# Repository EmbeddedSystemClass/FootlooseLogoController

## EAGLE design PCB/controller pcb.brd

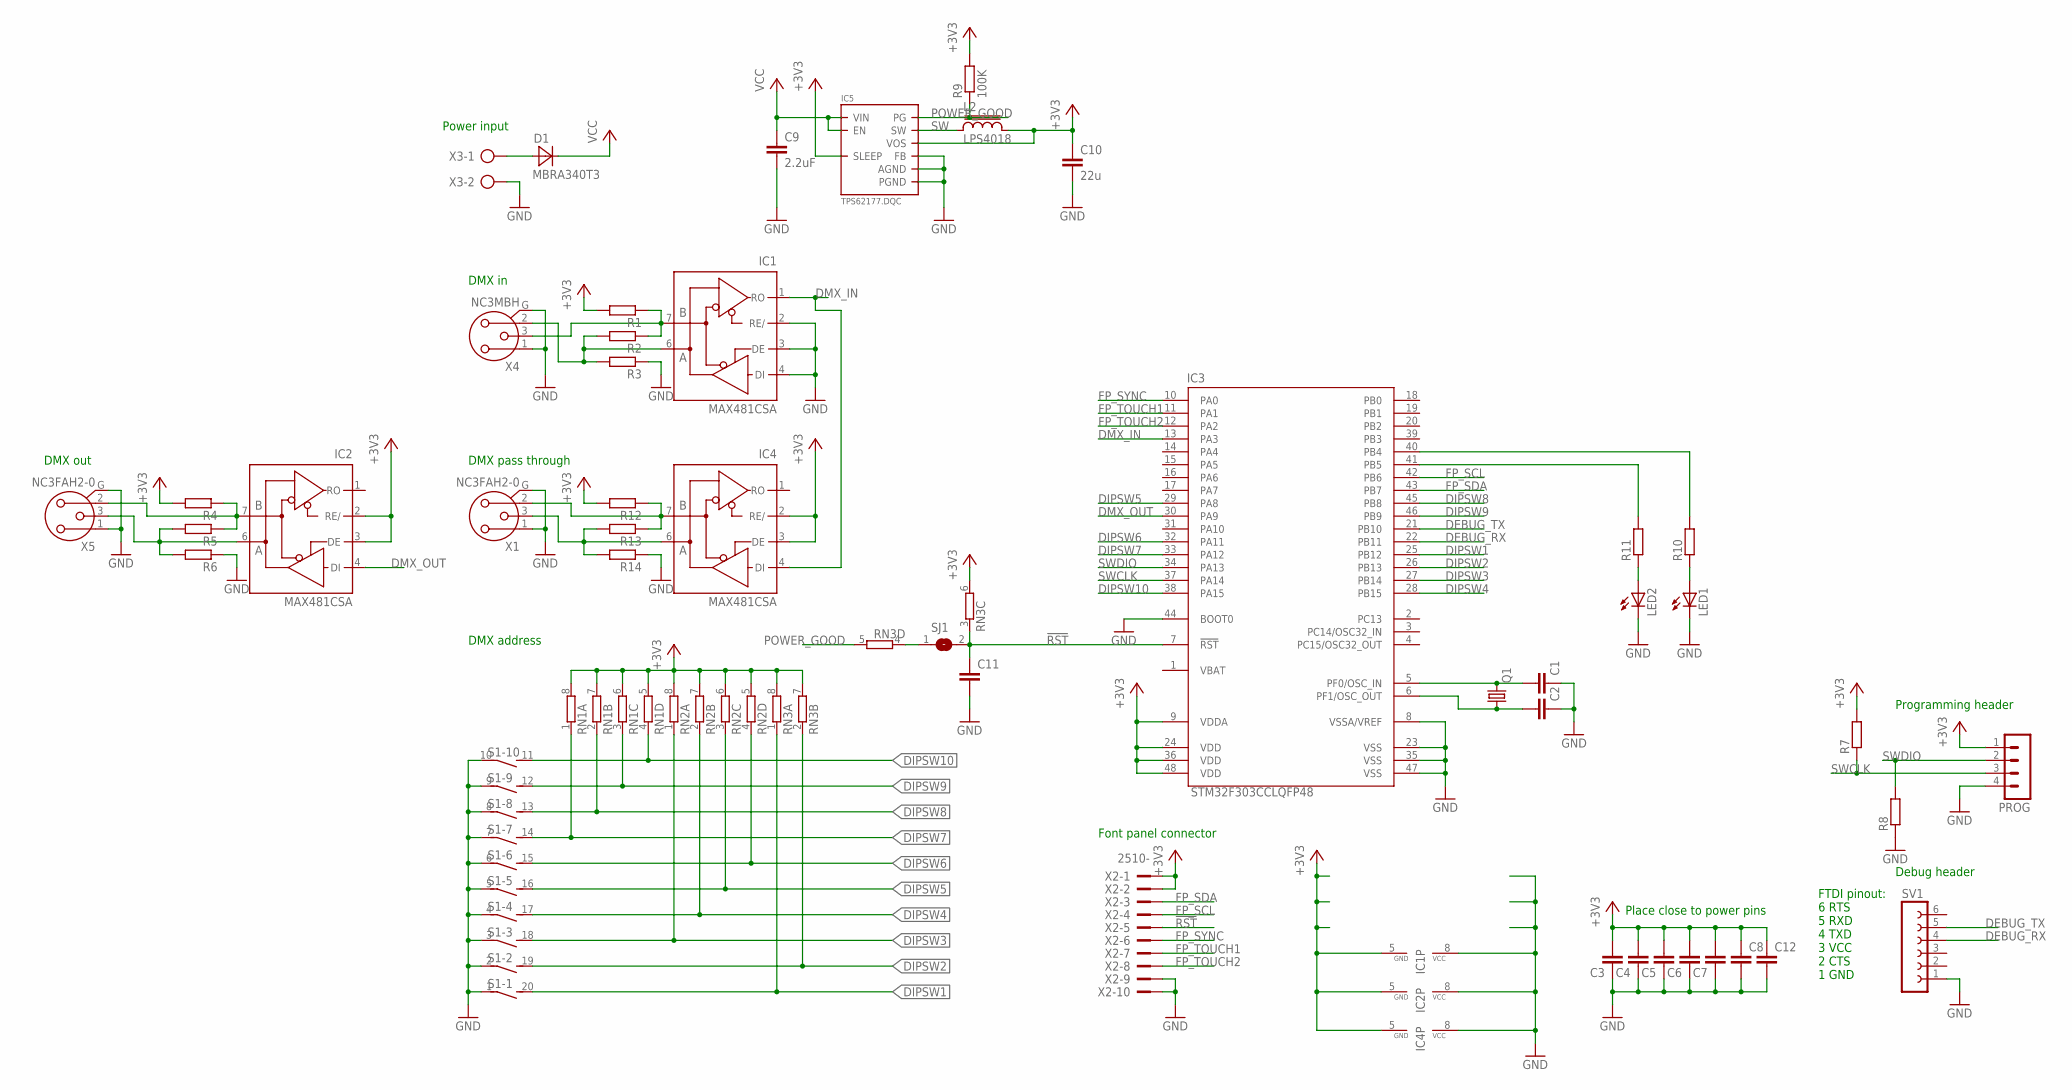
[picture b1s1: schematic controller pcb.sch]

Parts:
C1, C2, C3, C4, C5, C6, C7, C8, C11, C12: C-EUC0603K; C0603K
C9: 2.2uF; C1206
C10: 22u; C1206
D1: MBRA340T3; SMA
IC1, IC2, IC4: MAX481CSA; SO08
IC3: STM32F303CCLQFP48; LQFP48
IC5: TPS62177.DQC; DQC
L2: LPS4018
LED1, LED2: LEDCHIPLED_1206; CHIPLED_1206
PROG: MA04-1
Q1: CRYSTALCTS406; CTS406
R1, R2, R3, R4, R5, R6, R7, R8, R10, R11, R12, R13, R14: R-EU_R0603; R0603
R9: 100K; R0603
RN1, RN2, RN3: 4R-NCAY16; CAY16
S1: DIP10SB
SJ1: SJ
SV1: FE06-1; FE06
X1, X5: NC3FAH2-0
X2: 2510-; PAK100/2500-10
X3: AK500/2
X4: NC3MBH

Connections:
!RST: C11.1, IC3.7 (!RST), RN3.3 (1), SJ1.2, X2.5
+3V3: C3.2, C4.2, C5.2, C6.2, C7.2, C8.1, C10.1, C12.1, IC1.5 (GND), IC2.2 (RE/), IC2.3 (DE), IC2.5 (GND), IC3.9 (VDDA), IC3.24 (VDD), IC3.36 (VDD), IC3.48 (VDD), IC4.2 (RE/), IC4.3 (DE), IC4.5 (GND), IC5.8 (SLEEP), IC5.10 (VOS), L2.2, PROG.1, R1.2, R4.2, R7.2, R9.2, R12.2, RN1.5 (2), RN1.6 (2), RN1.7 (2), RN1.8 (2), RN2.5 (2), RN2.6 (2), RN2.7 (2), RN2.8 (2), RN3.6 (2), RN3.7 (2), RN3.8 (2), X2.1, X2.2
DEBUG_RX: IC3.22 (PB11), SV1.4
DEBUG_TX: IC3.21 (PB10), SV1.5
DIPSW1: IC3.25 (PB12), RN3.1, S1.20 (2)
DIPSW2: IC3.26 (PB13), RN3.2 (1), S1.19 (2)
DIPSW3: IC3.27 (PB14), RN2.1, S1.18 (2)
DIPSW4: IC3.28 (PB15), RN2.2 (1), S1.17 (2)
DIPSW5: IC3.29 (PA8), RN2.3 (1), S1.16 (2)
DIPSW6: IC3.32 (PA11), RN2.4 (1), S1.15 (2)
DIPSW7: IC3.33 (PA12), RN1.1, S1.14 (2)
DIPSW8: IC3.45 (PB8), RN1.2 (1), S1.13 (2)
DIPSW9: IC3.46 (PB9), RN1.3 (1), S1.12 (2)
DIPSW10: IC3.38 (PA15), RN1.4 (1), S1.11 (2)
DMX_IN: IC1.1 (RO), IC3.13 (PA3), IC4.4 (DI)
DMX_OUT: IC2.4 (DI), IC3.30 (PA9)
FP_SCL: IC3.42 (PB6), X2.4
FP_SDA: IC3.43 (PB7), X2.3
FP_SYNC: IC3.10 (PA0), X2.6
FP_TOUCH1: IC3.11 (PA1), X2.7
FP_TOUCH2: IC3.12 (PA2), X2.8
GND: C1.1, C2.1, C3.1, C4.1, C5.1, C6.1, C7.1, C8.2, C9.2, C10.2, C11.2, C12.2, IC1.2 (RE/), IC1.3 (DE), IC1.4 (DI), IC1.8 (VCC), IC2.8 (VCC), IC3.8 (VSSA/VREF), IC3.23 (VSS), IC3.35 (VSS), IC3.44 (BOOT0), IC3.47 (VSS), IC4.8 (VCC), IC5.1 (PGND), IC5.5 (FB), IC5.6 (AGND), IC5.PAD (PGND), LED1.C, LED2.C, PROG.4, R3.1, R6.1, R8.1, R14.1, S1.1, S1.2 (1), S1.3 (1), S1.4 (1), S1.5 (1), S1.6 (1), S1.7 (1), S1.8 (1), S1.9 (1), S1.10 (1), SV1.1, X1.1, X1.G, X2.9, X2.10, X3.2, X4.1, X4.G, X5.1, X5.G
unnamed: D1.A, X3.1
unnamed: IC4.6 (A), R13.2, R14.2, X1.3
unnamed: IC1.7 (B), R1.1, R2.1, X4.3
unnamed: C2.2, IC3.6 (PF1/OSC_OUT), Q1.1
unnamed: C1.2, IC3.5 (PF0/OSC_IN), Q1.3 (2)
unnamed: IC2.6 (A), R5.2, R6.2, X5.3
unnamed: IC2.7 (B), R4.1, R5.1, X5.2
unnamed: LED1.A, R10.1
unnamed: LED2.A, R11.1
unnamed: IC3.41 (PB5), R11.2
unnamed: IC3.40 (PB4), R10.2
unnamed: RN3.4 (1), SJ1.1
unnamed: IC4.7 (B), R12.1, R13.1, X1.2
unnamed: IC1.6 (A), R2.2, R3.2, X4.2
POWER_GOOD: IC5.7 (PG), R9.1, RN3.5 (2)
SW: IC5.9 (SW), L2.1
SWCLK: IC3.37 (PA14), PROG.3, R7.1
SWDIO: IC3.34 (PA13), PROG.2, R8.2
VCC: C9.1, D1.C, IC5.2 (VIN), IC5.3 (EN)

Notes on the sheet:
Power input
DMX in
DMX out
DMX address
Font panel connector
Place close to power pins
Debug header
FTDI pinout: 6 RTS 5 RXD 4 TXD 3 VCC 2 CTS 1 GND
Programming header
DMX pass through

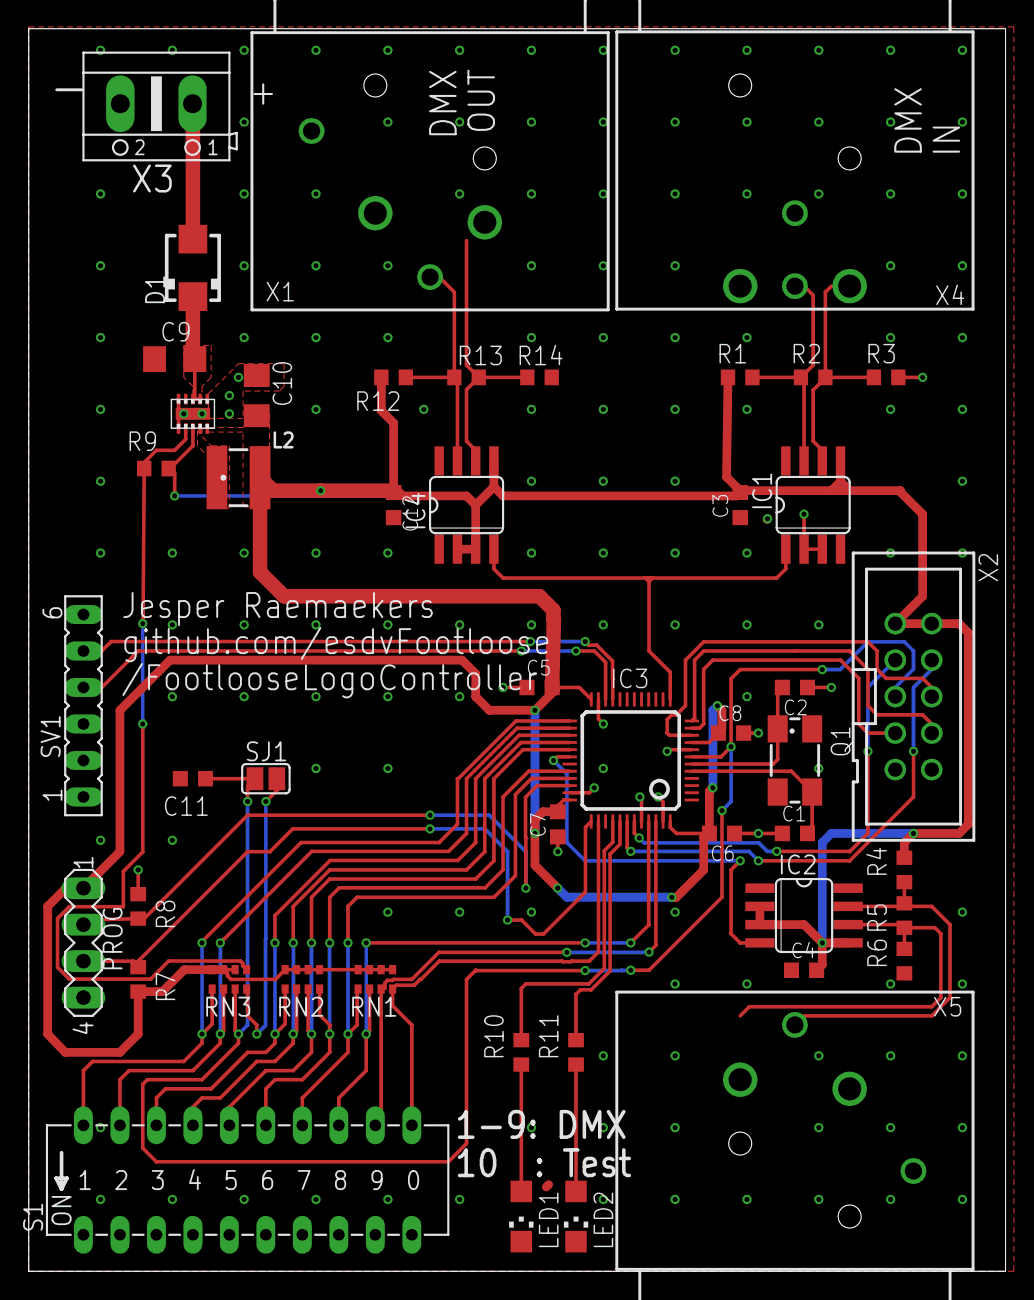
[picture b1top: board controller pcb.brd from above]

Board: 2 copper layers, 68.0 x 86.5 mm, 48 parts (0 on the bottom side), 41 nets.

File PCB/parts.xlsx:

Partlist
Exported from controller pcb.sch at 25/02/2019 09:50
EAGLE Version 9.3.0 Copyright (c) 1988-2019 Autodesk, Inc.
Assembly variant:
Part | Value | Device | Package | Library | Sheet | farnell code | amount
C1, C2 | 22pF | C-EUC0603K | C0603K | rcl | 1 | 2533830
C3, C4, C5, C6, C7, C8, C12 | 100nF | C-EUC0603K | C0603K | rcl | 1 | 2522395
C9 | 2.2uF | C-EUC1206 | C1206 | rcl | 1 | 1458911
C10 | 22u | C-EUC1206 | C1206 | rcl | 1
C11 | No | C-EUC0603K | C0603K | rcl | 1
D1 | MBRA340T3 | MBRA340T3 | SMA | diode | 1
IC1, IC2, IC4 | MAX481CSA | MAX481CSA | SO08 | maxim | 1 | 2519249
IC3 | STM32F303CCLQFP48 | STM32F303CCLQFP48 | LQFP48 | comp | 1 | 2215113
IC5 | TPS62177.DQC | TPS62177.DQC | DQC | packages(ti) | 1
L2 | LPS4018 | LPS4018 | LPS4018 | inductor-coilcraft | 1 | 2408076
LED1 |  | LEDCHIPLED_1206 | CHIPLED_1206 | led | 1 | 2099247
LED2 |  | LEDCHIPLED_1206 | CHIPLED_1206 | led | 1 | 2290336
PROG | Header 4P | MA04-1 | MA04-1 | con-lstb | 1
Q1 | 8MHz | CRYSTALCTS406 | CTS406 | crystal | 1
R1, R2, R3, R4, R5, R6, R12, R13, R14 |  | R-EU_R0603 | R0603 | rcl | 1
R7 |  | R-EU_R0603 | R0603 | rcl | 1
R8 |  | R-EU_R0603 | R0603 | rcl | 1
R9 | 100K | R-EU_R0603 | R0603 | rcl | 1
R10, R11 | 100 | R-EU_R0603 | R0603 | rcl | 1
RN1, RN2, RN3 | 4K7 | 4R-NCAY16 | CAY16 | resistor-dil | 1 | 2321746
S1 |  | DIP10SB | DIP10SB | switch-dil | 1 | 2468732
SV1 | Header 6P | FE06-1 | FE06 | con-lsta | 1
X1, X5 | NC3FAH2-0 | NC3FAH2-0 | NC3FAH2-0 | con-neutrik_ag | 1
X2 | Boxed header 10p | -2510 | PAK100/2500-10 | con-3m | 1
X3 | Power 2P | AK500/2 | AK500/2 | con-ptr500 | 1
X4 | NC3MBH | NC3MBH | NC3MBH | con-neutrik_ag | 1

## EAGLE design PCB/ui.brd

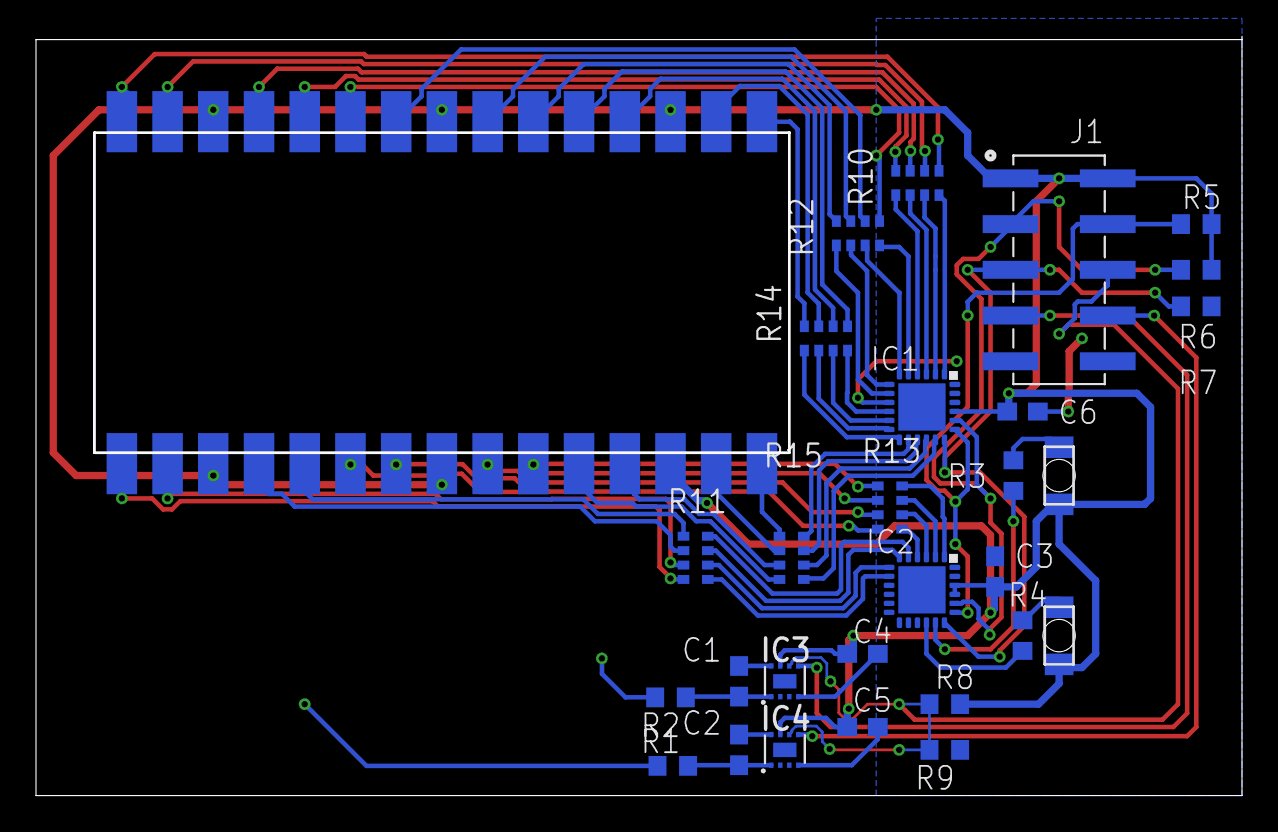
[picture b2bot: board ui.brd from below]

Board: 2 copper layers, 66.8 x 42.0 mm, 31 parts (26 on the bottom side), 64 nets.

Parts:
C1, C2, C3, C4, C5, C6: C0603
D1, D2: KPTL-3216; LED-REV
IC1, IC2: CAT9532; TQFN24-EP
IC3, IC4: AT42QT1011; UDFN/USON_8_PAD
J1: 610X1021121
R1, R2, R3, R4, R5, R6, R7, R8, R9: R0603
R10, R11, R12, R13, R14, R15: CAT16
SEG1, SEG2, SEG3: KCSA56-105; KCSA56-REV

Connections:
!RESET: IC1.18, IC2.18, J1.5, R7.2
+3V3: C3.1, C4.1, C5.1, C6.1, D1.P$1, D2.P$1, IC1.21, IC2.21, IC2.22, IC3.7, IC4.7, J1.1, J1.2, R5.2, R6.2, R8.2, SEG1.P3, SEG1.P8, SEG2.P3, SEG2.P8, SEG3.P3, SEG3.P8
GND: C3.2, C4.2, C5.2, C6.2, IC1.9, IC1.22, IC1.23, IC1.24, IC2.9, IC2.23, IC2.24, IC3.4, IC4.4, J1.9, J1.10, R7.1, R9.1
LED_PWR: IC2.17, R3.2
LED_STATUS: IC2.16, R4.2
unnamed: R10.8, SEG1.P10
unnamed: R10.7, SEG1.P9
unnamed: R10.6, SEG1.P7
unnamed: R10.5, SEG1.P6
unnamed: R12.8, SEG2.P10
unnamed: R12.7, SEG2.P9
unnamed: R12.6, SEG2.P7
unnamed: R12.5, SEG2.P6
unnamed: R14.8, SEG3.P10
unnamed: R14.7, SEG3.P9
unnamed: R14.6, SEG3.P7
unnamed: R14.5, SEG3.P6
unnamed: R11.8, SEG1.P5
unnamed: R11.7, SEG1.P4
unnamed: R11.6, SEG1.P2
unnamed: R11.5, SEG1.P1
unnamed: R13.8, SEG2.P5
unnamed: R13.7, SEG2.P4
unnamed: R13.6, SEG2.P2
unnamed: R13.5, SEG2.P1
unnamed: R15.8, SEG3.P5
unnamed: R15.7, SEG3.P4
unnamed: R15.6, SEG3.P2
unnamed: R15.5, SEG3.P1
unnamed: C1.1, IC3.1, R2.1
unnamed: C1.2, IC3.8
unnamed: D1.P$2, R3.1
unnamed: C2.1, IC4.1, R1.1
unnamed: C2.2, IC4.8
unnamed: D2.P$2, R4.1
SCL: IC1.19, IC2.19, J1.4, R5.1
SDA: IC1.20, IC2.20, J1.3, R6.1
SEGMENTA0: IC1.2, R10.3
SEGMENTA1: IC1.1, R10.4
SEGMENTA2: IC2.7, R11.2
SEGMENTA3: IC2.6, R11.3
SEGMENTA4: IC2.5, R11.4
SEGMENTA5: IC1.3, R10.2
SEGMENTA6: IC1.4, R10.1
SEGMENTA7: IC2.8, R11.1
SEGMENTB0: IC1.6, R12.3
SEGMENTB1: IC1.5, R12.4
SEGMENTB2: IC2.3, R13.2
SEGMENTB3: IC2.2, R13.3
SEGMENTB4: IC2.1, R13.4
SEGMENTB5: IC1.7, R12.2
SEGMENTB6: IC1.8, R12.1
SEGMENTB7: IC2.4, R13.1
SEGMENTC0: IC1.11, R14.3
SEGMENTC1: IC1.10, R14.4
SEGMENTC2: IC1.16, R15.2
SEGMENTC3: IC1.15, R15.3
SEGMENTC4: IC1.14, R15.4
SEGMENTC5: IC1.12, R14.2
SEGMENTC6: IC1.13, R14.1
SEGMENTC7: IC1.17, R15.1
SYNC: IC3.6, IC4.6, J1.6, R8.1, R9.2
TOUCH1: IC3.5, J1.7
TOUCH2: IC4.5, J1.8

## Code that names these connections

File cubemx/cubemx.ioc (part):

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Mcu.Name=STM32F303C(B-C)Tx
Mcu.Package=LQFP48
Mcu.UserName=STM32F303CCTx
PA10.Mode=Asynchronous
PA10.Signal=USART1_RX
PA13.Mode=Serial_Wire
PA13.Signal=SYS_JTMS-SWDIO
PA14.Mode=Serial_Wire
PA14.Signal=SYS_JTCK-SWCLK
PA15.Mode=Asynchronous
PA15.Signal=USART2_RX
PA2.Mode=Asynchronous
PA2.Signal=USART2_TX
PA3.Signal=S_TIM2_CH4
PA9.Mode=Asynchronous
PA9.Signal=USART1_TX
PB10.Mode=Asynchronous
PB10.Signal=USART3_TX
PB11.Mode=Asynchronous
PB11.Signal=USART3_RX
PB6.Mode=I2C
PB6.Signal=I2C1_SCL
PB7.Mode=I2C
PB7.Signal=I2C1_SDA
PC14-OSC32_IN.Mode=LSE-External-Oscillator
PC14-OSC32_IN.Signal=RCC_OSC32_IN
PC15-OSC32_OUT.Mode=LSE-External-Oscillator
PC15-OSC32_OUT.Signal=RCC_OSC32_OUT
PF0-OSC_IN.Mode=HSE-External-Oscillator
PF0-OSC_IN.Signal=RCC_OSC_IN
PF1-OSC_OUT.Mode=HSE-External-Oscillator
PF1-OSC_OUT.Signal=RCC_OSC_OUT
RCC.HSEPLLFreq_Value=8000000
RCC.HSE_VALUE=8000000
RCC.SYSCLKFreq_VALUE=72000000
RCC.SYSCLKSourceVirtual=RCC_SYSCLKSOURCE_PLLCLK
board=custom

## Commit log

2018-10-07 Initial commit
    Added eclipse project
    Added STMCubeMX project
    Added c++ support
    Added first test task
    Tested on HW
2018-10-09 Created serial driver concept
2018-10-13 initial draft oserror
    Draft using new oserror class. does not run yet
2018-11-08 Added c++ wrappers
2018-11-09 Updated OSError and added macro for accessing it
2018-11-09 Updated OSerror and drivers to use new semaphore
2018-11-12 Added driver for GPIO
2018-11-12 Added template for uart on STM32F103C8
2018-11-12 Added bin to dec decoder for inputs
2018-11-13 Added output blinker class. Updated cubemx project to enable software timers
2018-11-13 Created monitoring for future tasks to output on LED
2018-11-13 Started DMX receiver with rework of HAL uart
2018-11-14 Added DMX receiver interface
2018-11-14 Added light effect generator structure
2018-11-15 Increased heap size. Changed color setting in eclipse. EffectsController now working
2018-11-19 Added test effects and fixture sorting
2018-11-19 intermediate commit, nothing is working
2018-11-20 HAL uart can now send and receive data
2018-11-23 Timer interrupts working
2018-11-27 Adding timer to dmx receiver
2018-11-27 Added hal timer files
2018-11-27 Timer somewhat working, some values returning. fixed a seemingly simply mistake in hal files
2018-11-28 Set correct prescaler for timer
2018-11-29 Added dmx receiver logic
2018-12-03 Receiver working but with data offset.
2018-12-05 Initial commit of controller pcb
2018-12-09 ignoring eagle backup files
2018-12-09 Changed timer detection 3<>4 for correct edge detection
2018-12-09 removed debugging code
2018-12-11 added user interface pcb files
2018-12-12 UI PCB finished and slickscreen checked
2018-12-17 Minor changes to fron PCB. changed positioning of segments and buttons
2018-12-17 Draft of DMX transmitter
2019-01-13 DMX transmitter complete
2019-01-13 Linked effect controller to dmx transmitter
2019-02-03 Changed stack amount for most tasks, added new basic effect
2019-02-10 pending changes...
2019-02-12 Updated to STM32f303
2019-02-13 Placed extra decoupling cap and cleaned up some routing
2019-02-19 Finalized PCBs
2019-02-27 PCB parts list
2019-03-03 Porting to STM32f303CC. already changed in cubemx file
2019-03-03 Running on STM32F303
2019-03-03 Added power and status LEDs to BSP
2019-03-03 Corrected pin for LEDs
2019-03-16 Added missing interrupt handlers, changes task monitor led output. regenerated cubemx files with new version of cubemx
2019-03-17 Added I2C drivers and remote IO
2019-03-17 Added 7 segment driver
2019-03-26 Added state machine compiler
2019-04-28 Reworked timer and callback system
2019-04-28 Changed memory management
2019-04-28 Resolved stack overflow in BSP and fixed pinout for dipswitches
2019-05-01 Fixed UI IO mapping and added offset to bintodec converter
2019-05-02 Added semsaphore to I2C hal and auto update to the led drivers
2019-05-04 add brightness capability to driver and ui
2019-05-04 Added setenv template for SMC. added duplicate gpio class for output mirroring
2019-05-05 gpioduplicate not working yet
2019-05-05 GPIO duplicate was OK led driver toggle method was faulty
2019-05-18 Added effect controller to user interface, added new test effect, added effect mode selection
2019-05-18 Added UI states for test mode and wake up on dmx address change
2019-05-18 removed some warnings
2019-05-19 all warnings removed
2019-05-19 Reverted removal of default task
2019-06-30 Reverted to older HAL as uart receiving was not working
2019-07-01 Added timer file for STM32F3 series
2019-07-09 fixed pinout on pcb, added test effect
2019-07-21 improved ui
2019-07-31 Current state as in orbit. new effects added

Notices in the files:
parts and their libraries:
Eagle_BOARD-TO-BOARD_CONNECTORS: Copyright: Würth Elektronik
